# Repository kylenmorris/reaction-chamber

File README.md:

# Reaction Chamber for Pathogen Detection in Crops

Badges, platform, license, status

## About the Project
<!-- ##################### -->

Lorem ipsum dolor sit amet, consectetur adipiscing elit, sed do eiusmod tempor incididunt ut labore et dolore magna aliqua. Ut enim ad minim veniam, quis nostrud exercitation ullamco laboris nisi ut aliquip ex ea commodo consequat. 

## System Architecture
<!-- ##################### -->

### Block Diagram

### Images

### PCBs

## Software Architecture
<!-- ##################### -->

### Software Diagram

### State Diagram

### Hardware Abstraction

### Other Headers

## Hardware Overview
<!-- ##################### -->

## Design Decisions
<!-- ##################### -->

## Build and Flash Instructions
<!-- ##################### -->

### Prerequisites
* Raspberry Pi Pico SDK
  ```sh
  installation here
  ```
* CMake
  ```sh
  installation here
  ```

### Compilation and Flashing
While this project does make use of the Raspberry Pi Pico extension, there can be issues using it when first cloning the project. We are using CMake and Ninja for compilation, as is default for the Pico.
After pulling, navigate into the .\code\ directory
```
cd .\code
```
Create the build folder
```
New-Item -ItemType Directory -Name build ; cd build
```
Run CMake with Ninja, and build the project
```
cmake -G Ninja ..
ninja
```

### Running Tests

### License and Acknowledgements
MIT License 

Built for an industry partner as part of a capstone project. The implementation is original work.

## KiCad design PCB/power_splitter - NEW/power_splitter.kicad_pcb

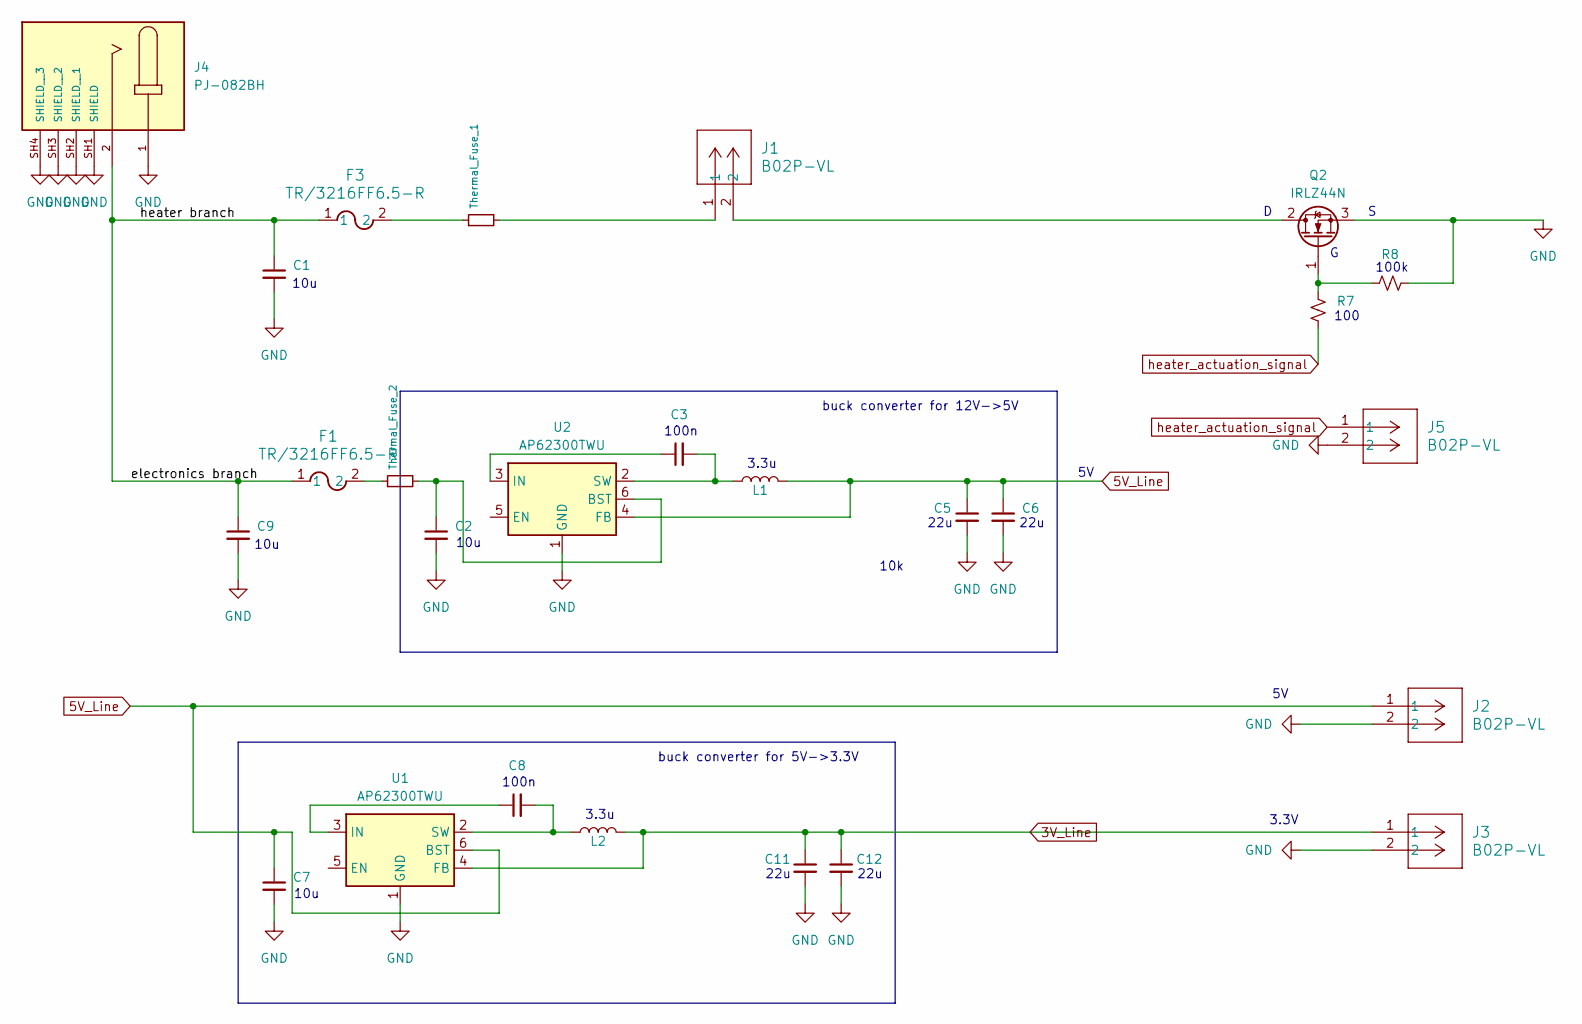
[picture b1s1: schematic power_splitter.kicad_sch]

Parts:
C1, C2, C3, C5, C6, C7, C8, C9, C11, C12: C_Small; C_1206_3216Metric_Pad1.33x1.80mm_HandSolder
F1, F3: TR/3216FF6.5-R; FUS_CB_3216FF
J1, J2, J3: B02P-VL; CONN_B02P-VL_JST
J4: PJ-082BH; SAMESKY_PJ-082BH; PARTREV 1.06
J5: B02P-VL; JST_NV_B02P-NV_1x02_P5.00mm_Vertical
L1, L2: L; L_Axial_L7.0mm_D3.3mm_P5.08mm_Vertical_Fastron_MICC
Q2: IRLZ44N; TO-220-3_Vertical
R7, R8: R_Small_US; YAG_MF25_YAG
Thermal_Fuse_1, Thermal_Fuse_2: R_Small; YAG_MF25_YAG
U1, U2: AP62300TWU; TSOT-23-6

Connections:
3V_Line: C11.1, C12.1, J3.1, L2.2, U1.4 (FB)
5V_Line: C5.1, C6.1, C7.1, J2.1, L1.2, U1.6 (BST), U2.4 (FB)
/electronics branch: C1.1, C9.1, F1.1, F3.1, J4.2
GND: C1.2, C2.2, C5.2, C6.2, C7.2, C9.2, C11.2, C12.2, J2.2, J3.2, J4.1, J4.SH1 (SHIELD), J4.SH2 (SHIELD__1), J4.SH3 (SHIELD__2), J4.SH4 (SHIELD__3), J5.2, Q2.3 (S), R8.2, U1.1 (GND), U2.1 (GND)
unnamed: F1.2, Thermal_Fuse_2.1
unnamed: F3.2, Thermal_Fuse_1.1
unnamed: J1.1, Thermal_Fuse_1.2
unnamed: J1.2, Q2.2 (D)
unnamed: Q2.1 (G), R7.1, R8.1
unnamed: C8.1, U1.3 (IN)
unnamed: C8.2, L2.1, U1.2 (SW)
unnamed: C2.1, Thermal_Fuse_2.2, U2.6 (BST)
unnamed: C3.1, U2.3 (IN)
unnamed: C3.2, L1.1, U2.2 (SW)
heater_actuation_signal: J5.1, R7.2

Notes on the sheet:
10u
100n
100
100k
10k
22u
3.3u
3.3V
buck converter for 12V->5V
buck converter for 5V->3.3V

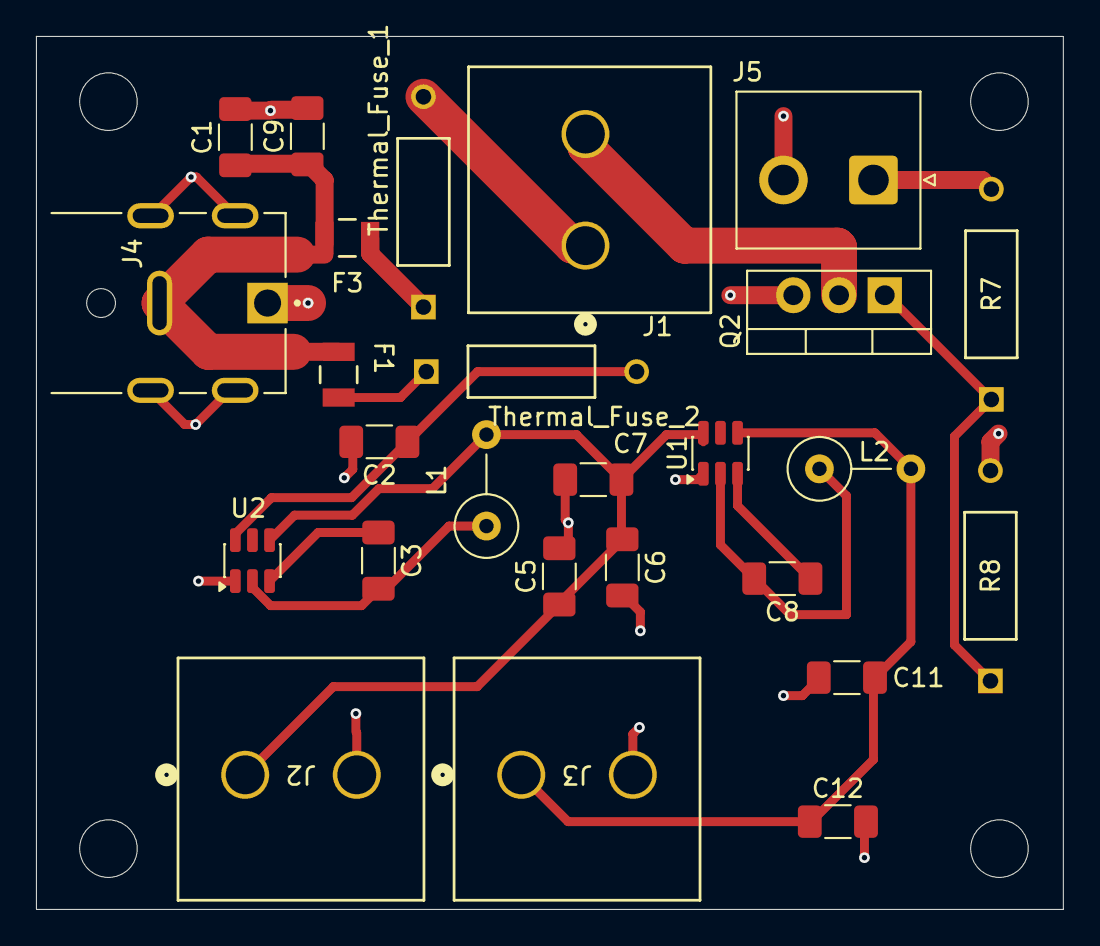
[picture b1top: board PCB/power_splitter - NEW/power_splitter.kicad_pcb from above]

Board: 2 copper layers, 57.1 x 48.5 mm, 26 parts (0 on the bottom side), 15 nets.

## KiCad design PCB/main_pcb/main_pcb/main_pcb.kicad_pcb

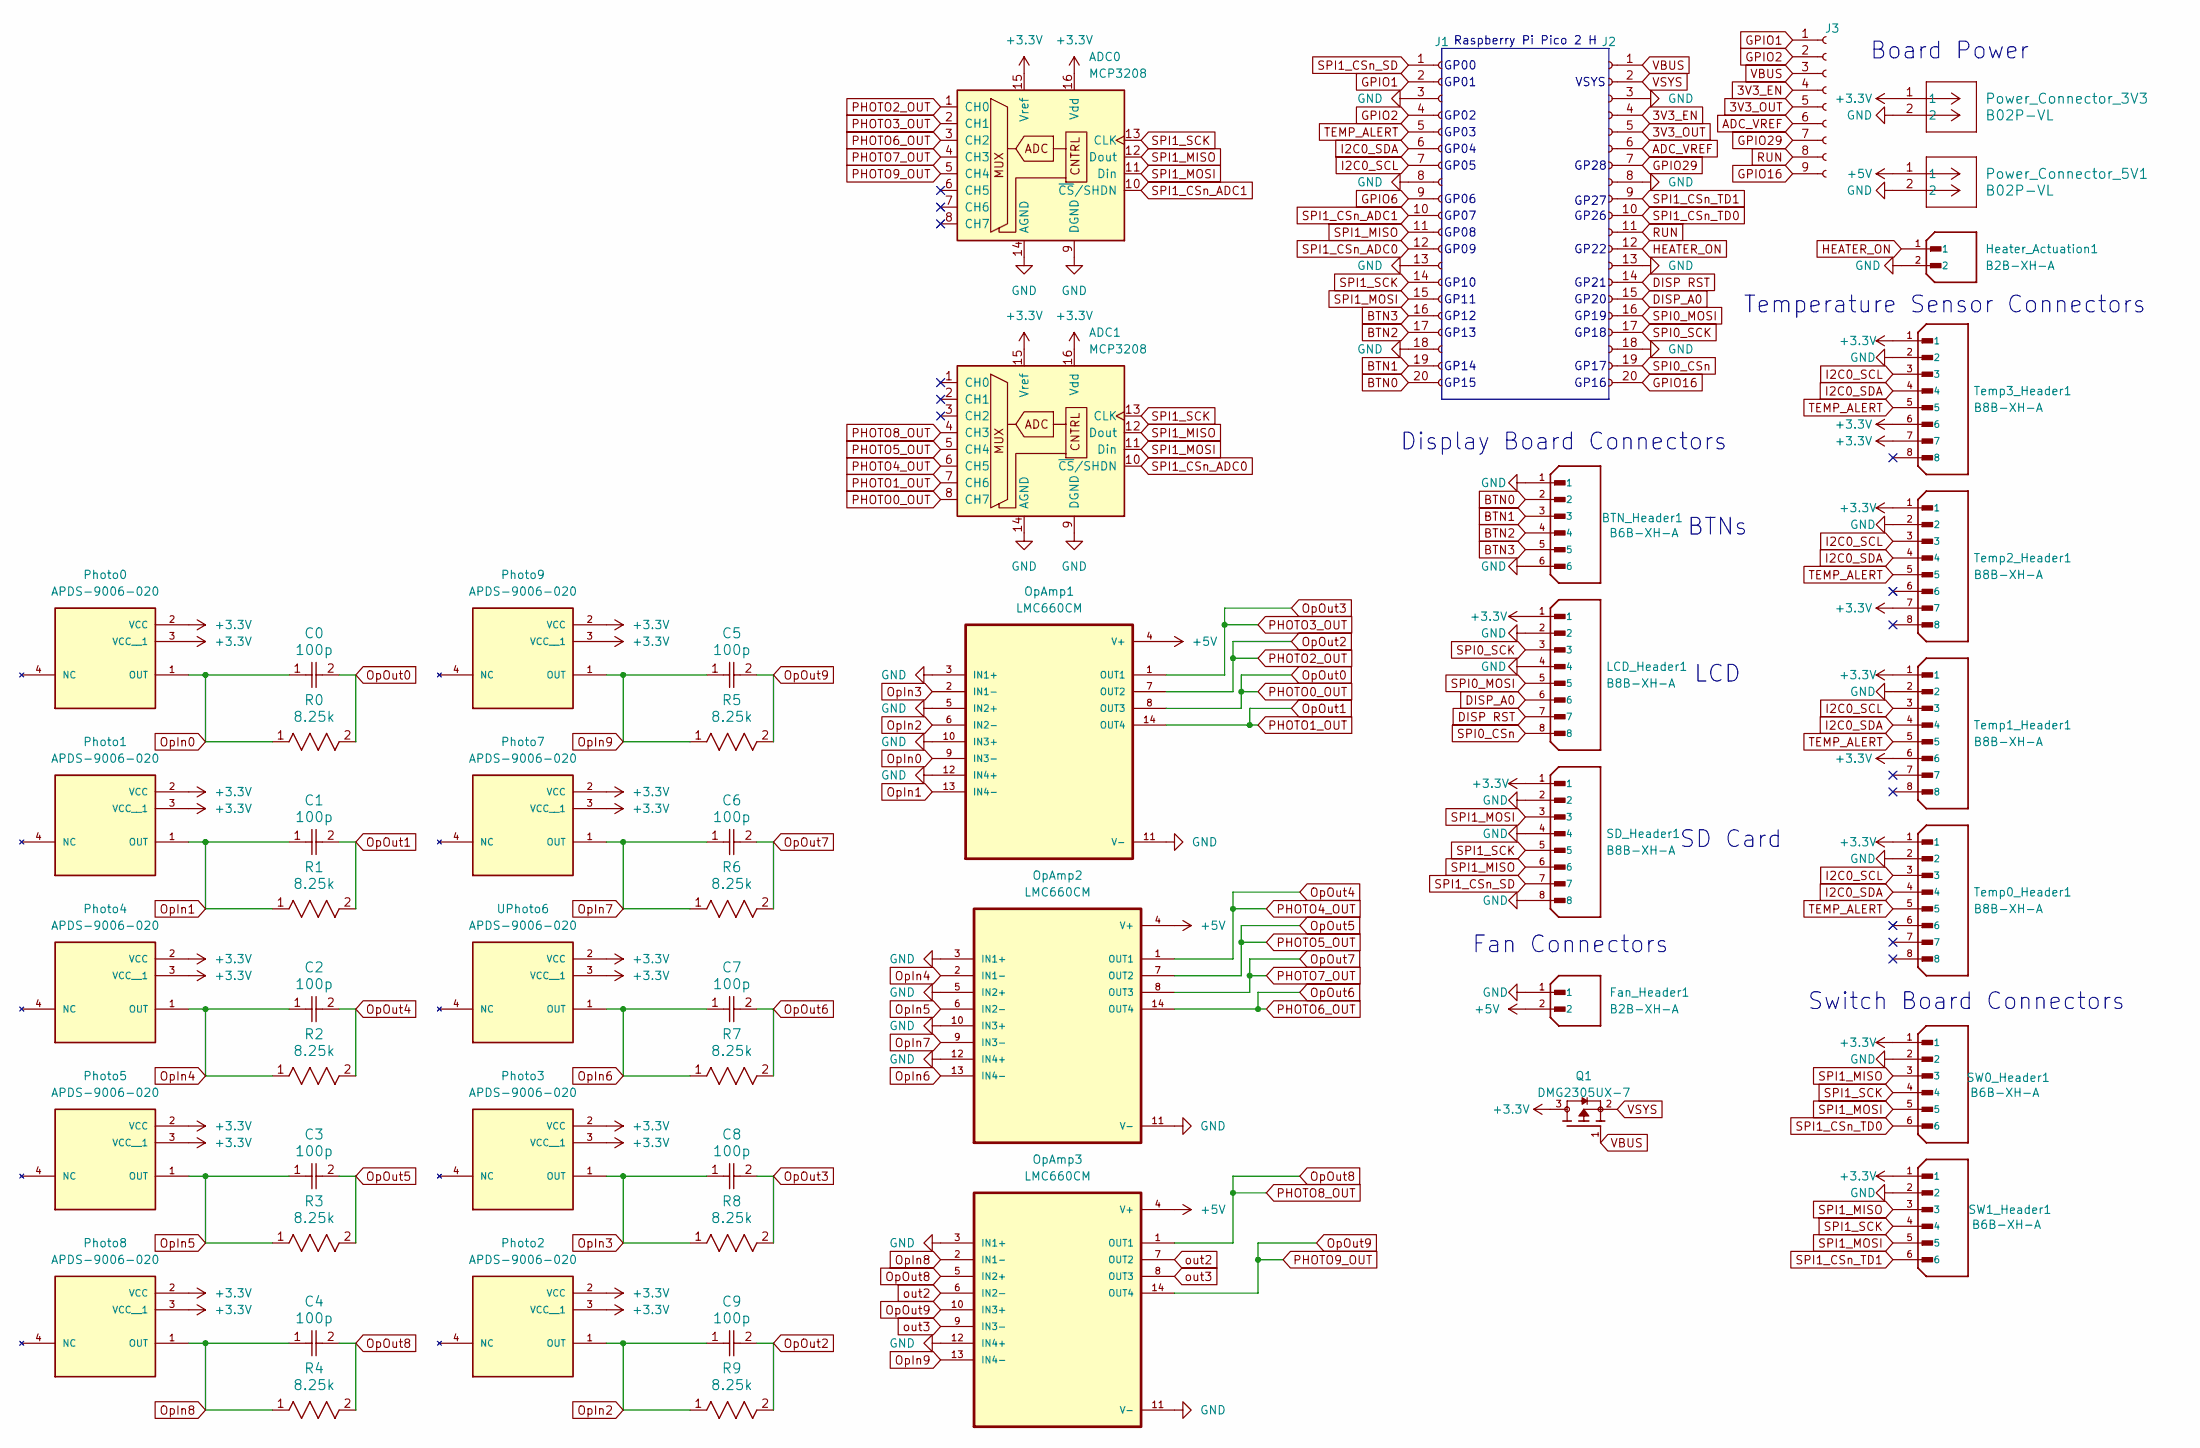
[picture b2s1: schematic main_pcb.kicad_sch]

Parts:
ADC0, ADC1: MCP3208; DIP254P762X432-16
BTN_Header1: B6B-XH-A; JST_XH_B6B-XH-A_1x06_P2.50mm_Vertical; PARTREV 7/4/21; DigiKey_Part_Number 455-B6B-XH-A-ND
C0, C1, C2, C3, C4, C5, C6, C7, C8, C9: 100p; C_1206_3216Metric_Pad1.33x1.80mm_HandSolder
Fan_Header1: B2B-XH-A; JST_B2B-XH-A; PARTREV N/A
Heater_Actuation1: B2B-XH-A; JST_B2B-XH-A; PARTREV N/A
J1, J2: Conn_01x20_Socket; PinSocket_1x20_P2.54mm_Vertical
J3: Conn_01x09_Socket; PinSocket_1x09_P2.54mm_Vertical
LCD_Header1: B8B-XH-A; JST_XH_B8B-XH-A_1x08_P2.50mm_Vertical; PARTREV 7/4/21
OpAmp1, OpAmp2, OpAmp3: LMC660CM; SOIC127P600X175-14N
Photo0, Photo1, Photo2, Photo3, Photo4, Photo5, Photo7, Photo8, Photo9: APDS-9006-020; photodiode_v4; PARTREV January 16, 2007
Power_Connector_3V3, Power_Connector_5V1: B02P-VL; CONN_B02P-VL_JST
Q1: DMG2305UX-7; SOT91P240X110-3N_DMG2305UX-7; PARTREV 09/2018
R0, R1, R2, R3, R4, R5, R6, R7, R8, R9: 8.25k; YAG_MF25_YAG
SD_Header1: B8B-XH-A; JST_XH_B8B-XH-A_1x08_P2.50mm_Vertical; PARTREV 7/4/21
SW0_Header1, SW1_Header1: B6B-XH-A; JST_XH_B6B-XH-A_1x06_P2.50mm_Vertical; PARTREV 7/4/21; DigiKey_Part_Number 455-B6B-XH-A-ND
Temp0_Header1, Temp1_Header1, Temp2_Header1, Temp3_Header1: B8B-XH-A; JST_XH_B8B-XH-A_1x08_P2.50mm_Vertical; PARTREV 7/4/21
UPhoto6: APDS-9006-020; photodiode_v4; PARTREV January 16, 2007

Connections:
3V3_EN: J2.4, J3.4
3V3_OUT: J2.5, J3.5
+3.3V: ADC0.15 (Vref), ADC0.16 (Vdd), ADC1.15 (Vref), ADC1.16 (Vdd), LCD_Header1.1, Photo0.2 (VCC), Photo0.3 (VCC__1), Photo1.2 (VCC), Photo1.3 (VCC__1), Photo2.2 (VCC), Photo2.3 (VCC__1), Photo3.2 (VCC), Photo3.3 (VCC__1), Photo4.2 (VCC), Photo4.3 (VCC__1), Photo5.2 (VCC), Photo5.3 (VCC__1), Photo7.2 (VCC), Photo7.3 (VCC__1), Photo8.2 (VCC), Photo8.3 (VCC__1), Photo9.2 (VCC), Photo9.3 (VCC__1), Power_Connector_3V3.1, Q1.3, SD_Header1.1, SW0_Header1.1, SW1_Header1.1, Temp0_Header1.1, Temp1_Header1.1, Temp1_Header1.6, Temp2_Header1.1, Temp2_Header1.7, Temp3_Header1.1, Temp3_Header1.6, Temp3_Header1.7, UPhoto6.2 (VCC), UPhoto6.3 (VCC__1)
+5V: Fan_Header1.2, OpAmp1.4 (V+), OpAmp2.4 (V+), OpAmp3.4 (V+), Power_Connector_5V1.1
ADC_VREF: J2.6, J3.6
BTN0: BTN_Header1.2, J1.20
BTN1: BTN_Header1.3, J1.19
BTN2: BTN_Header1.4, J1.17
BTN3: BTN_Header1.5, J1.16
DISP RST: J2.14, LCD_Header1.7
DISP_A0: J2.15, LCD_Header1.6
GND: ADC0.9 (DGND), ADC0.14 (AGND), ADC1.9 (DGND), ADC1.14 (AGND), BTN_Header1.1, BTN_Header1.6, Fan_Header1.1, Heater_Actuation1.2, J1.3, J1.8, J1.13, J1.18, J2.3, J2.8, J2.13, J2.18, LCD_Header1.2, LCD_Header1.4, OpAmp1.3 (IN1+), OpAmp1.5 (IN2+), OpAmp1.10 (IN3+), OpAmp1.11 (V-), OpAmp1.12 (IN4+), OpAmp2.3 (IN1+), OpAmp2.5 (IN2+), OpAmp2.10 (IN3+), OpAmp2.11 (V-), OpAmp2.12 (IN4+), OpAmp3.3 (IN1+), OpAmp3.11 (V-), OpAmp3.12 (IN4+), Power_Connector_3V3.2, Power_Connector_5V1.2, SD_Header1.2, SD_Header1.4, SD_Header1.8, SW0_Header1.2, SW1_Header1.2, Temp0_Header1.2, Temp1_Header1.2, Temp2_Header1.2, Temp3_Header1.2
GPIO1: J1.2, J3.1
GPIO2: J1.4, J3.2
GPIO6: J1.9
GPIO16: J2.20, J3.9
GPIO29: J2.7, J3.7
HEATER_ON: Heater_Actuation1.1, J2.12
I2C0_SCL: J1.7, Temp0_Header1.3, Temp1_Header1.3, Temp2_Header1.3, Temp3_Header1.3
I2C0_SDA: J1.6, Temp0_Header1.4, Temp1_Header1.4, Temp2_Header1.4, Temp3_Header1.4
OpIn0: C0.1, OpAmp1.9 (IN3-), Photo0.1 (OUT), R0.1
OpIn1: C1.1, OpAmp1.13 (IN4-), Photo1.1 (OUT), R1.1
OpIn2: C9.1, OpAmp1.6 (IN2-), Photo2.1 (OUT), R9.1
OpIn3: C8.1, OpAmp1.2 (IN1-), Photo3.1 (OUT), R8.1
OpIn4: C2.1, OpAmp2.2 (IN1-), Photo4.1 (OUT), R2.1
OpIn5: C3.1, OpAmp2.6 (IN2-), Photo5.1 (OUT), R3.1
OpIn6: C7.1, OpAmp2.13 (IN4-), R7.1, UPhoto6.1 (OUT)
OpIn7: C6.1, OpAmp2.9 (IN3-), Photo7.1 (OUT), R6.1
OpIn8: C4.1, OpAmp3.2 (IN1-), Photo8.1 (OUT), R4.1
OpIn9: C5.1, OpAmp3.13 (IN4-), Photo9.1 (OUT), R5.1
OpOut0: ADC1.8 (CH7), C0.2, OpAmp1.8 (OUT3), R0.2
OpOut1: ADC1.7 (CH6), C1.2, OpAmp1.14 (OUT4), R1.2
OpOut2: ADC0.1 (CH0), C9.2, OpAmp1.7 (OUT2), R9.2
OpOut3: ADC0.2 (CH1), C8.2, OpAmp1.1 (OUT1), R8.2
OpOut4: ADC1.6 (CH5), C2.2, OpAmp2.1 (OUT1), R2.2
OpOut5: ADC1.5 (CH4), C3.2, OpAmp2.7 (OUT2), R3.2
OpOut6: ADC0.3 (CH2), C7.2, OpAmp2.14 (OUT4), R7.2
OpOut7: ADC0.4 (CH3), C6.2, OpAmp2.8 (OUT3), R6.2
OpOut8: ADC1.4 (CH3), C4.2, OpAmp3.1 (OUT1), OpAmp3.5 (IN2+), R4.2
OpOut9: ADC0.5 (CH4), C5.2, OpAmp3.10 (IN3+), OpAmp3.14 (OUT4), R5.2
RUN: J2.11, J3.8
SPI0_CSn: J2.19, LCD_Header1.8
SPI0_MOSI: J2.16, LCD_Header1.5
SPI0_SCK: J2.17, LCD_Header1.3
SPI1_CSn_ADC0: ADC1.10 (~CS/SHDN), J1.12
SPI1_CSn_ADC1: ADC0.10 (~CS/SHDN), J1.10
SPI1_CSn_SD: J1.1, SD_Header1.7
SPI1_CSn_TD0: J2.10, SW0_Header1.6
SPI1_CSn_TD1: J2.9, SW1_Header1.6
SPI1_MISO: ADC0.12 (Dout), ADC1.12 (Dout), J1.11, SD_Header1.6, SW0_Header1.3, SW1_Header1.3
SPI1_MOSI: ADC0.11 (Din), ADC1.11 (Din), J1.15, SD_Header1.3, SW0_Header1.5, SW1_Header1.5
SPI1_SCK: ADC0.13 (CLK), ADC1.13 (CLK), J1.14, SD_Header1.5, SW0_Header1.4, SW1_Header1.4
TEMP_ALERT: J1.5, Temp0_Header1.5, Temp1_Header1.5, Temp2_Header1.5, Temp3_Header1.5
VBUS: J2.1, J3.3, Q1.1
VSYS: J2.2, Q1.2
out2: OpAmp3.6 (IN2-), OpAmp3.7 (OUT2)
out3: OpAmp3.8 (OUT3), OpAmp3.9 (IN3-)

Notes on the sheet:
GP18
GP06
GP11
Switch Board Connectors
GP12
GP27
SD Card
GP22
Fan Connectors
GP10
GP15
GP03
GP09
GP21
VSYS
GP05
GP16
Display Board Connectors
GP04
GP02
GP13
Temperature Sensor Connectors
GP14
GP17
GP00
Board Power
GP19
GP28
LCD
GP20
GP07
GP08
BTNs
GP26
Raspberry Pi Pico 2 H
GP01

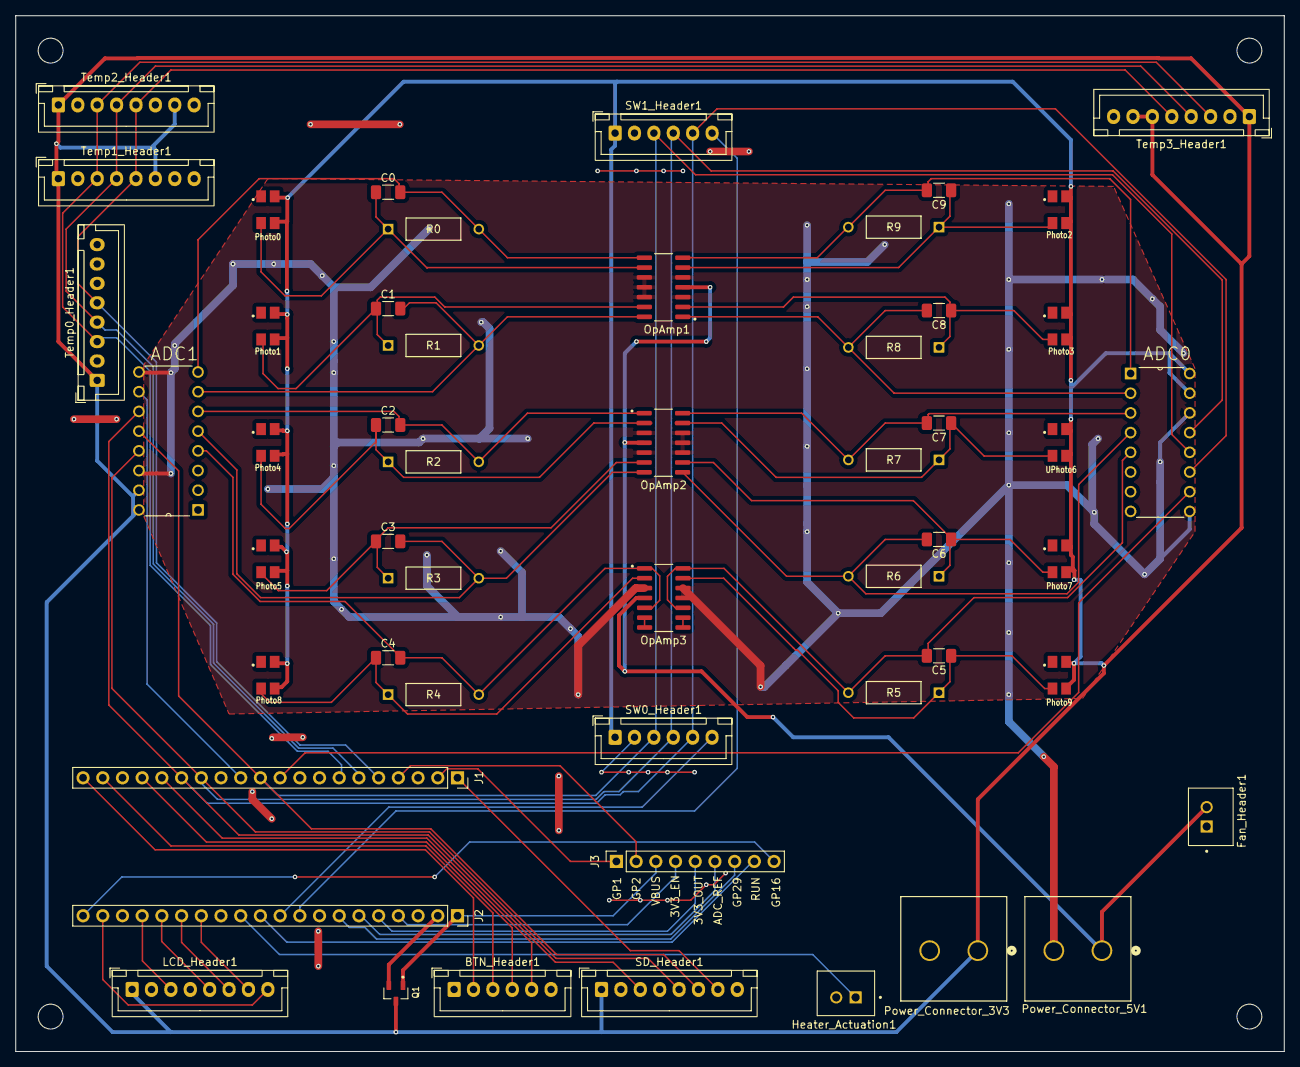
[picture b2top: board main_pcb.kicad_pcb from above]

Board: 2 copper layers, 163.5 x 133.5 mm, 52 parts (0 on the bottom side), 56 nets.

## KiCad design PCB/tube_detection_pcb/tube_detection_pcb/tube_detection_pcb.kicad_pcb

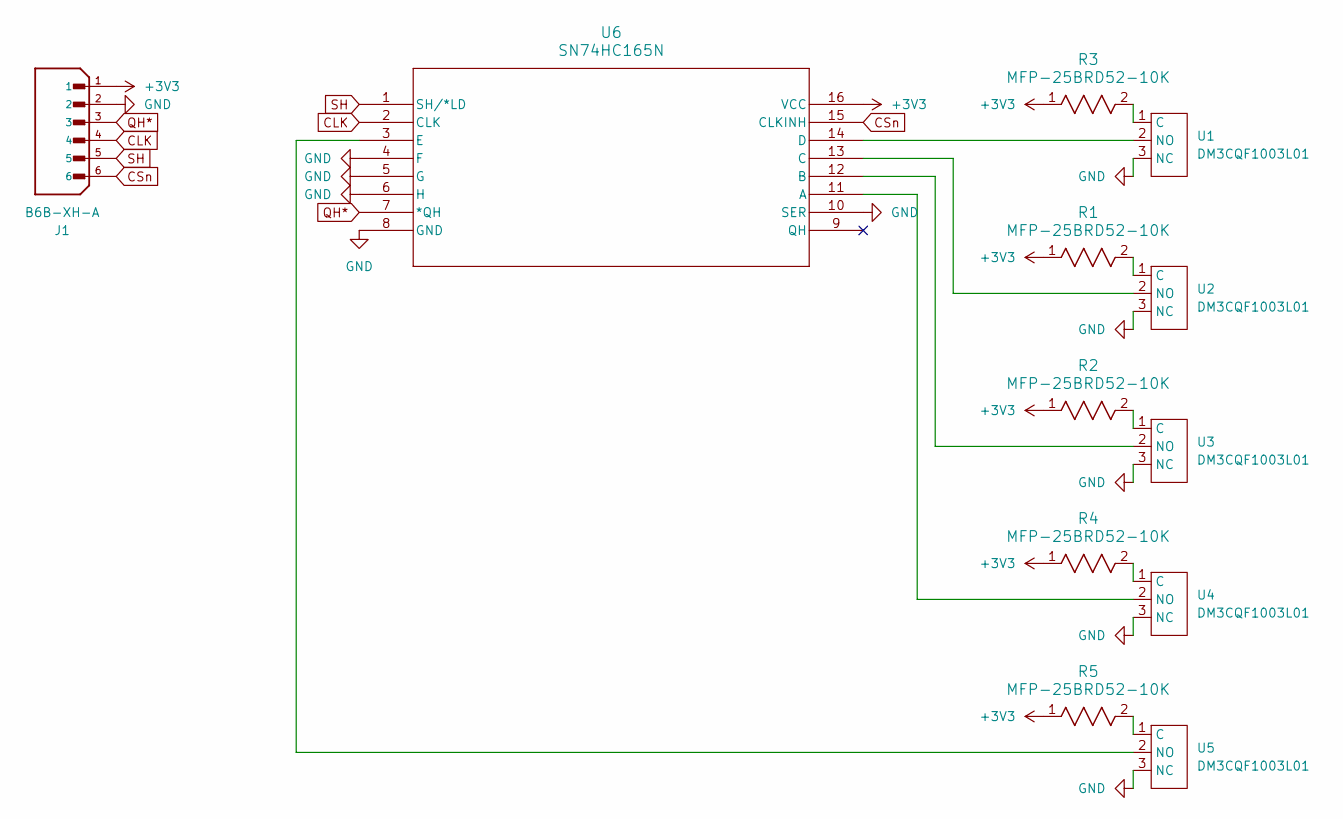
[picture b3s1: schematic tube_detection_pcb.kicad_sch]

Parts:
J1: B6B-XH-A; JST_XH_B6B-XH-A_1x06_P2.50mm_Vertical; PARTREV 7/4/21; DigiKey_Part_Number 455-B6B-XH-A-ND
R1, R2, R3, R4, R5: MFP-25BRD52-10K; YAG_MF25_YAG
U1, U2, U3, U4, U5: DM3CQF1003L01
U6: SN74HC165N; N16

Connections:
+3V3: J1.1, R1.1, R2.1, R3.1, R4.1, R5.1, U6.16 (VCC)
CLK: J1.4, U6.2 (CLK)
CSn: J1.6, U6.15 (CLKINH)
GND: J1.2, U1.3 (NC), U2.3 (NC), U3.3 (NC), U4.3 (NC), U5.3 (NC), U6.4 (F), U6.5 (G), U6.6 (H), U6.8 (GND), U6.10 (SER)
unnamed: R3.2, U1.1 (C)
unnamed: U1.2 (NO), U6.14 (D)
unnamed: R1.2, U2.1 (C)
unnamed: U2.2 (NO), U6.13 (C)
unnamed: R2.2, U3.1 (C)
unnamed: U3.2 (NO), U6.12 (B)
unnamed: R4.2, U4.1 (C)
unnamed: U4.2 (NO), U6.11 (A)
unnamed: R5.2, U5.1 (C)
unnamed: U5.2 (NO), U6.3 (E)
QH*: J1.3, U6.7 (*QH)
SH: J1.5, U6.1 (SH/*LD)

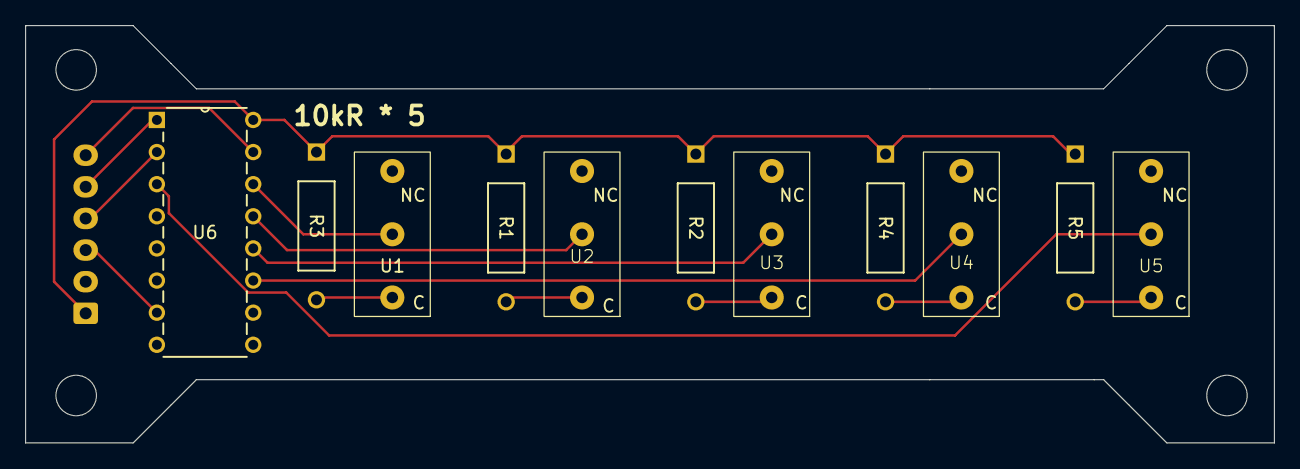
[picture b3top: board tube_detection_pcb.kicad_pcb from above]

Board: 2 copper layers, 98.8 x 33.0 mm, 12 parts (1 on the bottom side), 16 nets.

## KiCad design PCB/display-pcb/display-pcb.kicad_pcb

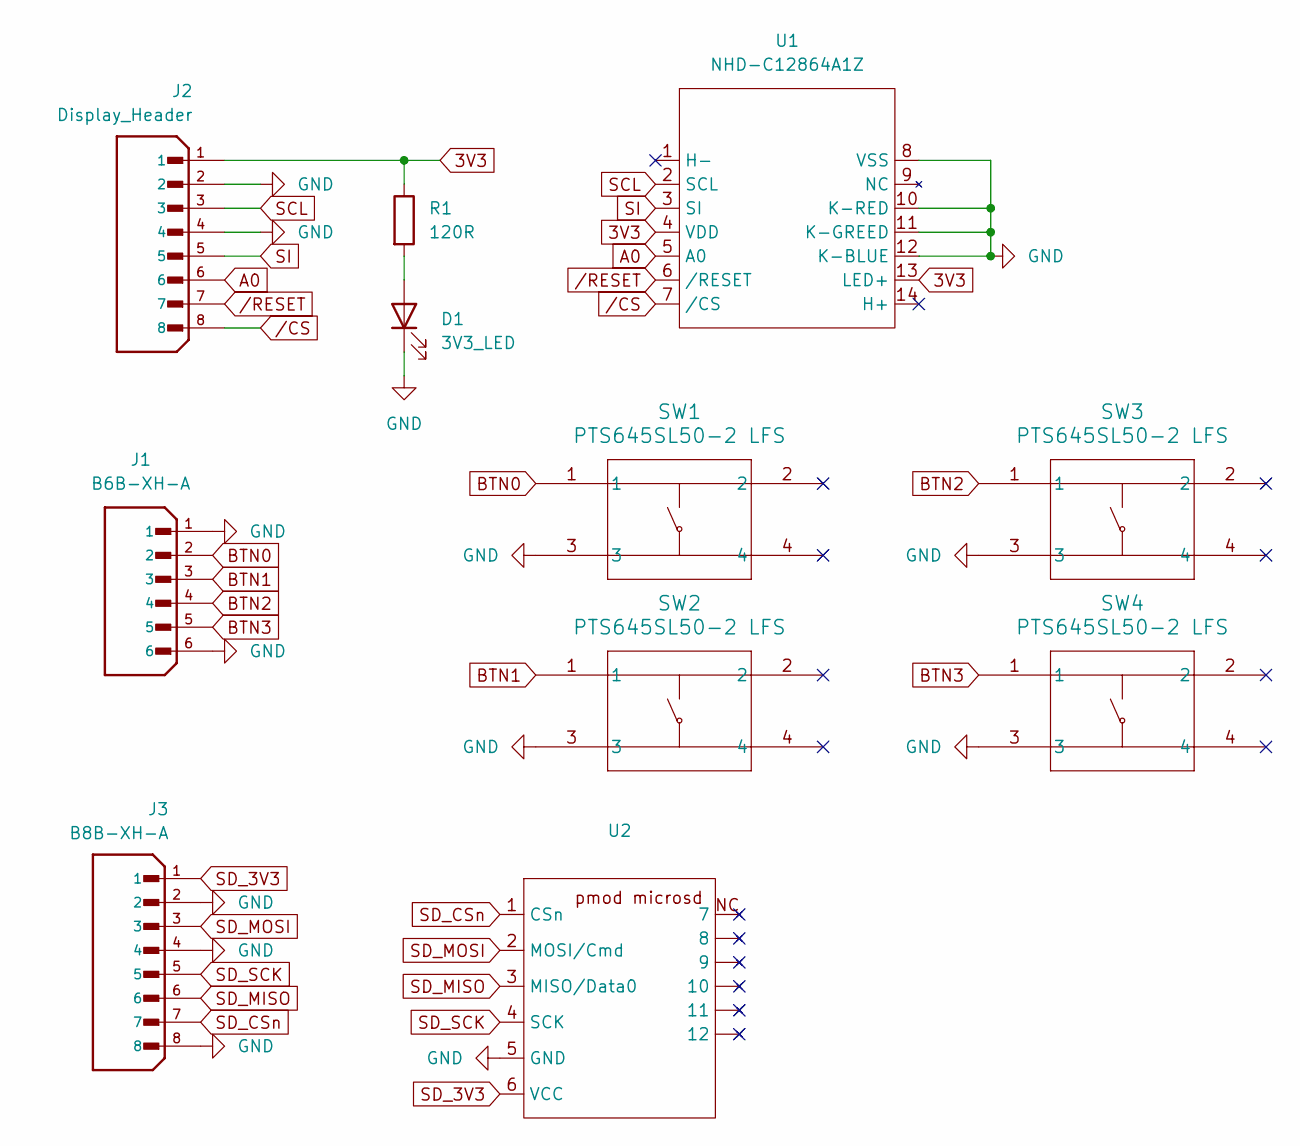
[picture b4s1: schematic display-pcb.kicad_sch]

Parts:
D1: 3V3_LED; LED_D3.0mm
J1: B6B-XH-A; JST_XH_B6B-XH-A_1x06_P2.50mm_Vertical; PARTREV 7/4/21; DigiKey_Part_Number 455-B6B-XH-A-ND
J2: Display_Header; JST_XH_B8B-XH-A_1x08_P2.50mm_Vertical; PARTREV 7/4/21
J3: B8B-XH-A; JST_XH_B8B-XH-A_1x08_P2.50mm_Vertical; PARTREV 7/4/21
R1: 120R; YAG_MF25_YAG
SW1, SW2, SW3, SW4: PTS645SL50-2 LFS; PTS654S_CNK
U1: NHD-C12864A1Z
U2: pmod-microsd

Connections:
3V3: J2.1, R1.1, U1.4 (VDD), U1.13 (LED+)
A0: J2.6, U1.5 (A0)
BTN0: J1.2, SW1.1
BTN1: J1.3, SW2.1
BTN2: J1.4, SW3.1
BTN3: J1.5, SW4.1
GND: D1.1 (K), J1.1, J1.6, J2.2, J2.4, J3.2, J3.4, J3.8, SW1.3, SW2.3, SW3.3, SW4.3, U1.8 (VSS), U1.10 (K-RED), U1.11 (K-GREED), U1.12 (K-BLUE), U2.5 (GND)
unnamed: D1.2 (A), R1.2
SCL: J2.3, U1.2 (SCL)
SD_3V3: J3.1, U2.6 (VCC)
SD_CSn: J3.7, U2.1 (CSn)
SD_MISO: J3.6, U2.3 (MISO/Data0)
SD_MOSI: J3.3, U2.2 (MOSI/Cmd)
SD_SCK: J3.5, U2.4 (SCK)
SI: J2.5, U1.3 (SI)
/CS: J2.8, U1.7 (/CS)
/RESET: J2.7, U1.6 (/RESET)

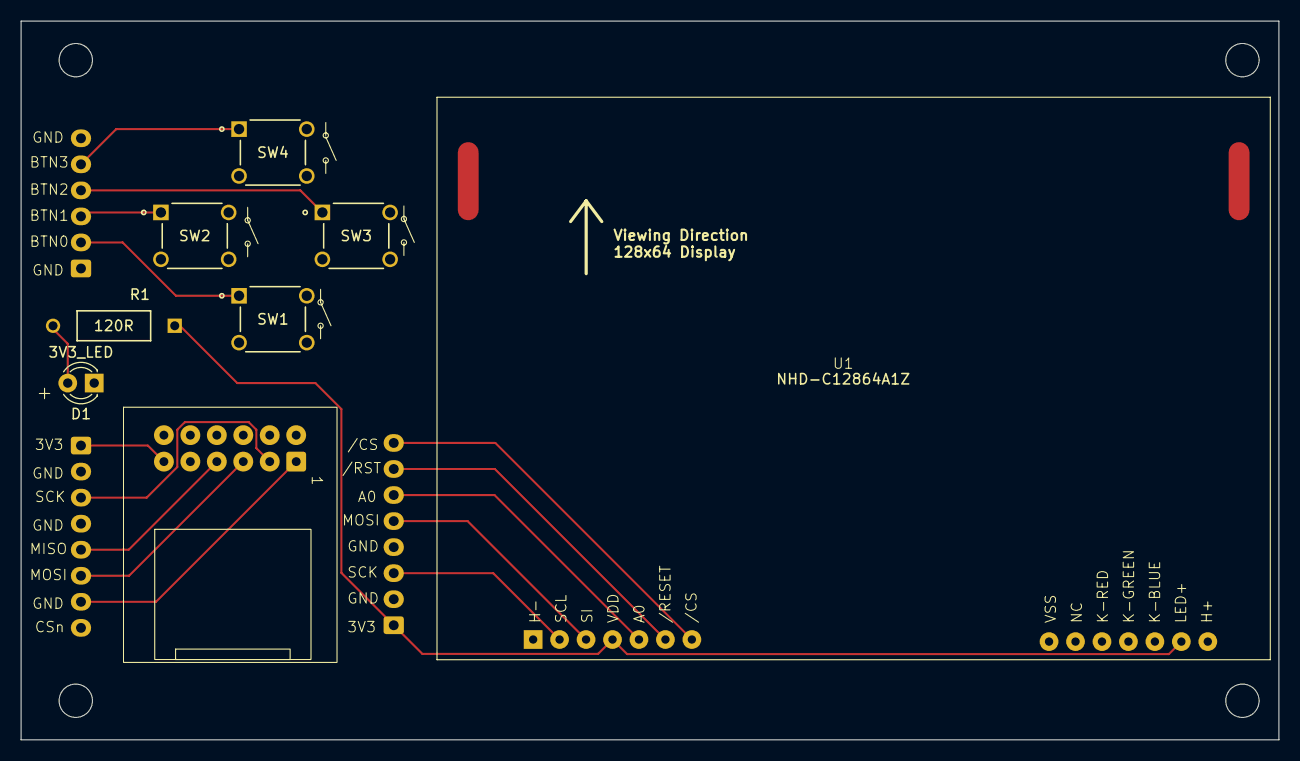
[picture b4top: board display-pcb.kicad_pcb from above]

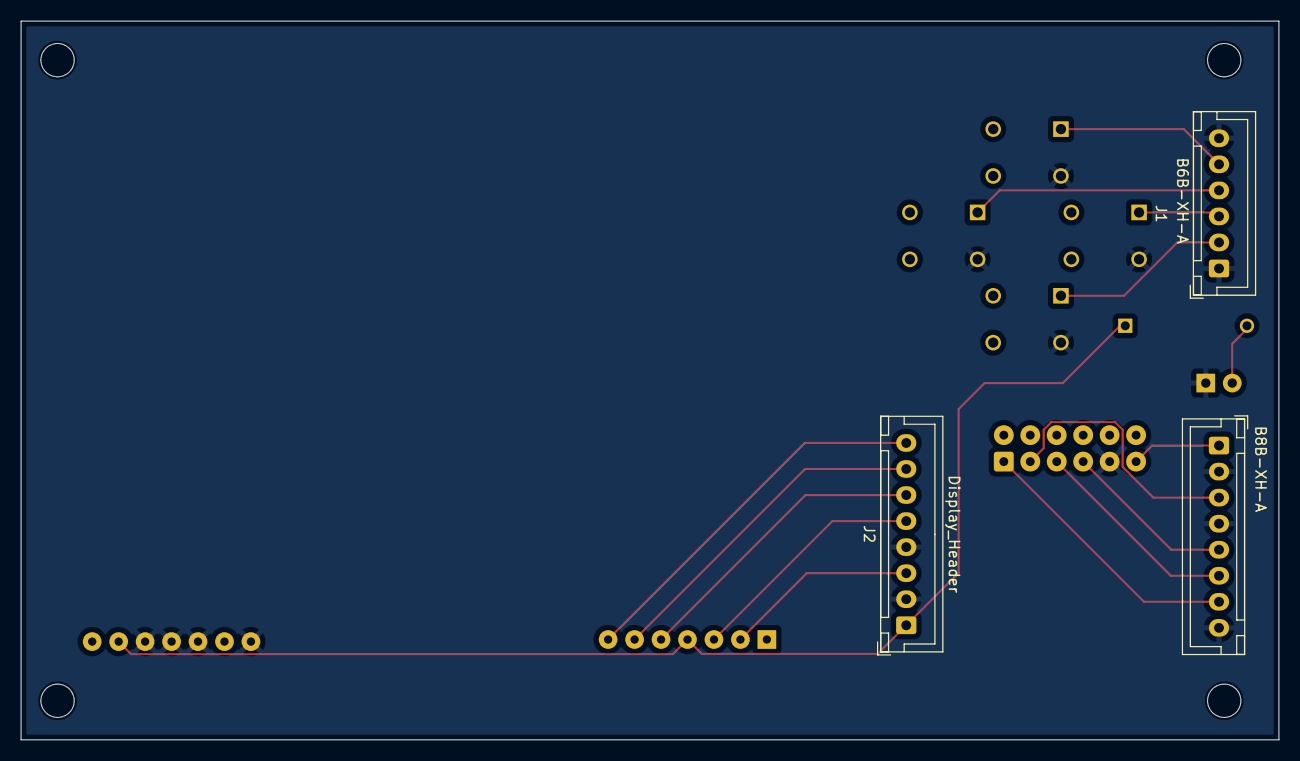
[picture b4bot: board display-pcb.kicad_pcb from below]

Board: 2 copper layers, 120.8 x 69.0 mm, 11 parts (3 on the bottom side), 17 nets.

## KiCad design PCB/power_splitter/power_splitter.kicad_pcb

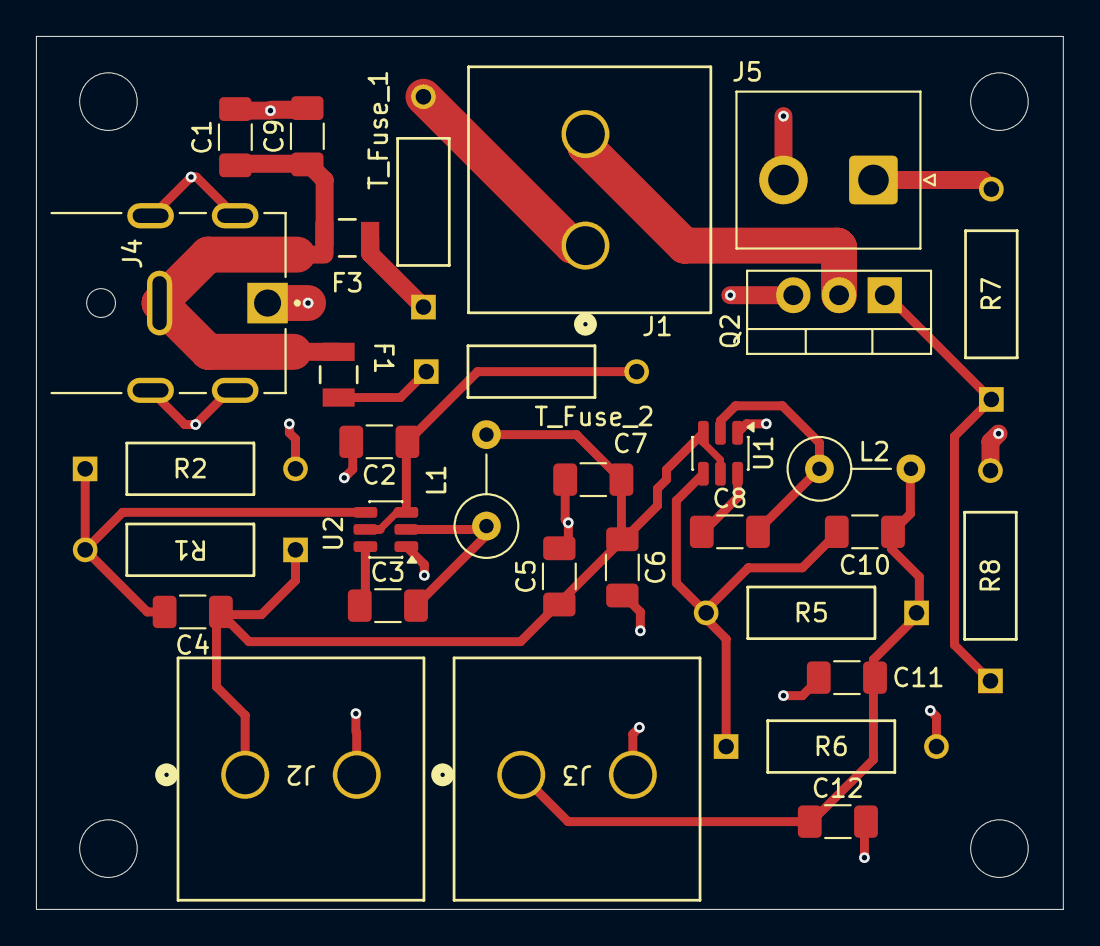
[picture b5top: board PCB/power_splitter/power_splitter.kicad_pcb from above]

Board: 2 copper layers, 57.1 x 48.5 mm, 32 parts (0 on the bottom side), 17 nets.

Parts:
C1, C2, C3, C4, C5, C6, C7, C8, C9, C10, C11, C12: C_Small; C_1206_3216Metric_Pad1.33x1.80mm_HandSolder
F1, F3: TR/3216FF6.5-R; FUS_CB_3216FF
J1, J2, J3: B02P-VL; CONN_B02P-VL_JST
J4: PJ-082BH; SAMESKY_PJ-082BH
J5: B02P-VL; JST_NV_B02P-NV_1x02_P5.00mm_Vertical
L1, L2: L; L_Axial_L7.0mm_D3.3mm_P5.08mm_Vertical_Fastron_MICC
Q2: IRLZ44N; TO-220-3_Vertical
R1, R2, R5, R6: R_Small; YAG_MF25_YAG
R7, R8: R_Small_US; YAG_MF25_YAG
T_Fuse_1, T_Fuse_2: R_Small; YAG_MF25_YAG
U1, U2: AP62300TWU; TSOT-23-6

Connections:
3V_Line: C10.1, C11.1, C12.1, J3.1, L2.2, R5.1
5V_Line: C4.1, C5.1, C6.1, C7.1, J2.1, L1.2, R1.1, U1.3 (IN), U1.5 (EN)
/electronics branch: C1.1, C9.1, F1.1, F3.1, J4.2
GND: C1.2, C2.2, C5.2, C6.2, C7.2, C9.2, C11.2, C12.2, J2.2, J3.2, J4.1, J4.SH1 (SHIELD), J4.SH2 (SHIELD__1), J4.SH3 (SHIELD__2), J4.SH4 (SHIELD__3), J5.2, Q2.3 (S), R2.2, R6.2, R8.2, U1.1 (GND), U2.1 (GND)
unnamed: F1.2, T_Fuse_2.1
unnamed: F3.2, T_Fuse_1.1
unnamed: J1.1, T_Fuse_1.2
unnamed: J1.2, Q2.2 (D)
unnamed: Q2.1 (G), R7.1, R8.1
unnamed: C8.1, U1.6 (BST)
unnamed: C10.2, R5.2, R6.1, U1.4 (FB)
unnamed: C8.2, L2.1, U1.2 (SW)
unnamed: C3.1, U2.6 (BST)
unnamed: C2.1, T_Fuse_2.2, U2.3 (IN), U2.5 (EN)
unnamed: C4.2, R1.2, R2.1, U2.4 (FB)
unnamed: C3.2, L1.1, U2.2 (SW)
heater_actuation_signal: J5.1, R7.2

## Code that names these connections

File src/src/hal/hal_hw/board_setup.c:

#include "drivers.h"

#include "constants.h"
#include <stdbool.h>
#include <hardware/gpio.h>
#include <hardware/spi.h>
#include <hardware/i2c.h>

#include "ff.h"
#include "glcd.h"

#ifdef CYW43_WL_GPIO_LED_PIN
#include "pico/cyw43_arch.h"
#endif

int init_led(void) {
    #if defined(PICO_DEFAULT_LED_PIN)
        // A device like Pico that uses a GPIO for the LED will define PICO_DEFAULT_LED_PIN
        // so we can use normal GPIO functionality to turn the led on and off
        gpio_init(PICO_DEFAULT_LED_PIN);
        gpio_set_dir(PICO_DEFAULT_LED_PIN, GPIO_OUT);
        return PICO_OK;
    #elif defined(CYW43_WL_GPIO_LED_PIN)
        // For Pico W devices we need to initialise the driver etc
        return cyw43_arch_init();
    #endif
}

static void init_gpio_as_button(int gpio_pin) {
    gpio_init(gpio_pin);
    gpio_set_dir(gpio_pin, GPIO_IN);
    gpio_pull_up(gpio_pin);
}

void board_setup(void) {

    #ifdef USE_HW_PICO

        stdio_init_all();
        init_led();

        // Spi 0
        spi_init(spi0, SPI0_BAUDRATE);     
        
        gpio_set_function(SPI0_SCK_PIN, GPIO_FUNC_SPI);
        // gpio_set_function(SPI0_MISO_PIN, GPIO_FUNC_SPI);
        gpio_set_function(SPI0_MOSI_PIN, GPIO_FUNC_SPI);

        // Spi 1
        spi_init(spi1, SPI1_BAUDRATE);       
        
        gpio_set_function(SPI1_SCK_PIN, GPIO_FUNC_SPI);
        gpio_set_function(SPI1_MISO_PIN, GPIO_FUNC_SPI);
        gpio_set_function(SPI1_MOSI_PIN, GPIO_FUNC_SPI);

        // Buttons
        for (int i = 0; i < NUM_BUTTONS; i++) {
            init_gpio_as_button(BUTTON_PINS[i]);
        }

        // Heater
        gpio_init(HEATER_PIN);
        gpio_set_dir(HEATER_PIN, GPIO_OUT);
        gpio_put(HEATER_PIN, 0); // make sure heater is off to start

        // Display
        gpio_init(SPI0_CSn_DISPLAY_PIN);
        gpio_set_dir(SPI0_CSn_DISPLAY_PIN, GPIO_OUT);
        gpio_put(SPI0_CSn_DISPLAY_PIN, HIGH); // Deselect

        gpio_set_function(SPI0_CSn_DISPLAY_PIN, GPIO_FUNC_SPI); 

        // Photodiodes
        gpio_init(SPI1_CSn_ADC0_PIN);
        gpio_set_dir(SPI1_CSn_ADC0_PIN, GPIO_OUT);
        gpio_put(SPI1_CSn_ADC0_PIN, 1);

        gpio_init(SPI1_CSn_ADC1_PIN);
        gpio_set_dir(SPI1_CSn_ADC1_PIN, GPIO_OUT);
        gpio_put(SPI1_CSn_ADC1_PIN, 1);

        // Temperature sensors
        i2c_init(i2c0, I2C_BAUDRATE);
        gpio_set_function(I2C_SDA_PIN, GPIO_FUNC_I2C);
        gpio_set_function(I2C_SCL_PIN, GPIO_FUNC_I2C);
        gpio_pull_up(I2C_SDA_PIN);
        gpio_pull_up(I2C_SCL_PIN);

        // Tube switches
        gpio_init(SPI1_CS_SHIFT_SWITCHES_SR_PIN_0);
        gpio_set_dir(SPI1_CS_SHIFT_SWITCHES_SR_PIN_0, GPIO_OUT);
        gpio_put(SPI1_CS_SHIFT_SWITCHES_SR_PIN_0, 1);
        
        gpio_init(SPI1_CS_SHIFT_SWITCHES_SR_PIN_1);
        gpio_set_dir(SPI1_CS_SHIFT_SWITCHES_SR_PIN_1, GPIO_OUT);
        gpio_put(SPI1_CS_SHIFT_SWITCHES_SR_PIN_1, 1);

        gpio_init(1);
        gpio_set_dir(1, GPIO_OUT);
        gpio_put(1, 1);

        // SD card reader
        // gpio_init(SPI1_CS0_PIN);
        // gpio_set_dir(SPI1_CS0_PIN, GPIO_OUT);
        // gpio_put(SPI1_CS0_PIN, HIGH); // Deselect
        // i think glcd does this

        // Debug pin
        gpio_init(PROBE_PIN);
        gpio_set_dir(PROBE_PIN, GPIO_IN);

        // Libraries
        glcd_init();


    #else

    #endif

}
